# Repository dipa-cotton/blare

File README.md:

# blare
my annoying alarm clock :)

## purpose
i wanted to make this alarm clock to familiarize myself with C++ and the arduino IDE. i really enjoyed playing around with the pcb as well, it was a fun mini project!

## goals
i want to submit this to blare to hopefully get the pillowcase :) I'll sleep better knowing orpheus is watching over me... or i guess under me

## components
the main files are my PCB and Schematic made in kicad, and I have directories of my arduino code and my case's stl file as well :)

no ai was used in this project :))))))

## pictures

## BOM
- 6 Cherry MX Switches
- 1 LCD Display
- 1 Lolin C3 Mini
- 1 Buzzer
- 6 Diodes
- 3 Capacitors (already owned)
a more detailed list can be found in BOM.csv :)

## Journal
### Day 1: PCB
#### Hours Spent: 3
##### What did you do?:
Today, I used KiCAD to build the schematic for my alarm as well as routed the PCB. This took quite a bit of effort, and took me a couple of hours due to fixing ERC and DRC issues.

##### Why did you do it?:
I did this to create the PCB for my project, so it can be easily manufactured and used to make an alarm clock that is compact for its size :)

##### What problems did you face?:
I faced issues with ERC (electric rules checker), mostly unused pins lol. In the end though, with google by my side, I was able to figure out that the unused pins must have an x symbol at the end of them to prevent KiCAD from getting angered. In the images above, you can see the specific wiring of the components, as well as the final PCB. The PCB was the easy part, as routing was quite simple.

### Day 2: Code
#### Hours Spent: 4
##### What did you do?:
Today, I used the Arduino IDE to fully code the alarm clock. In my code, there are if statements that correspond each switch to a certain command, which displays what it does on the LCD as well. There are multiple commands, such as one that displays an undertale doggo, one that shows the weather, one that allows you to set an alarm time, one that shows the current time, and others as well. This code, once uploaded should hopefully turn the alarm clock into a working device, not just an alarm clock :)

##### Why did you do it?:
I did this with the goal of making something more complex than a simple alarm clock, but a device within itself that can be used for multiple purposes, sort of like a nightstand hub that tells you everything you need to know!

##### What problems did you face?:
I faced syntax issues with C++ as always, and I also didn't know how to display an image of the undertale doggo on the screen, but with guidance from google and a website that turned the image into a format that the c3 can understand, I was able to successfully use it to display an image when a certain button is pressed. In the future, I may try to add motion, or a lil gif of the guy jumping!

### Day 3: CAD
#### Hours Spent: 1
##### What did you do?:
Today, I used Fusion 360 to create a case for my alarm clock. I exported a step file of the pcb from KiCAD, imported it into Fusion as a mesh file, and created a case around it. This process made sure that everything is correctly spaced, and looks nice.

##### Why did you do it?:
I did this so the alarm clock isn't just a PCB with no case. It has a heart too, yknow? In the future, I'll make it look nicer, but once my PCB arrives, I'll make sure everything fits and make it look nicer.

##### What problems did you face?:
I didn't really face any issues, cuz I know Fusion 360 pretty well, but text always acts funny on my Mac so I just had to struggle with that for a minute or 2.

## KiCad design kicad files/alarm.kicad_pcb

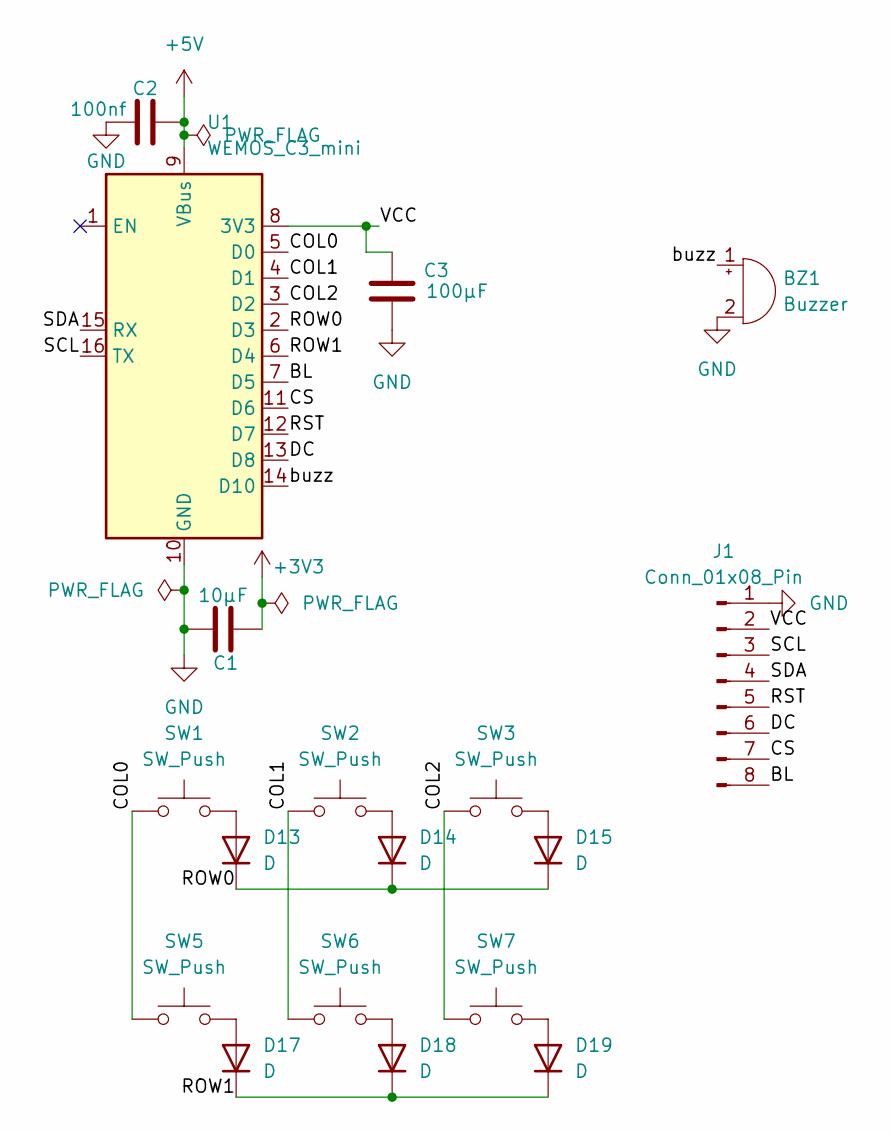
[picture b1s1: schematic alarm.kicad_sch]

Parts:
BZ1: Buzzer; Buzzer_12x9.5RM7.6
C1: 10µF; CP_Axial_L10.0mm_D4.5mm_P15.00mm_Horizontal
C2: 100nf; CP_Axial_L10.0mm_D4.5mm_P15.00mm_Horizontal
C3: 100µF; CP_Axial_L10.0mm_D4.5mm_P15.00mm_Horizontal
D13, D14, D15, D17, D18, D19: D; D_T-1_P10.16mm_Horizontal
J1: Conn_01x08_Pin; PinHeader_1x08_P2.54mm_Vertical
SW1, SW2, SW3, SW5, SW6, SW7: SW_Push; SW_Cherry_MX_1.00u_PCB
U1: WEMOS_C3_mini

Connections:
+3V3: C1.2
+5V: C2.2, U1.9 (VBus)
/BL: J1.8, U1.7 (D5)
/COL0: SW1.1, SW5.1, U1.5 (D0)
/COL1: SW2.1, SW6.1, U1.4 (D1)
/COL2: SW3.1, SW7.1, U1.3 (D2)
/CS: J1.7, U1.11 (D6)
/DC: J1.6, U1.13 (D8)
/ROW0: D13.1 (K), D14.1 (K), D15.1 (K), U1.2 (D3)
/ROW1: D17.1 (K), D18.1 (K), D19.1 (K), U1.6 (D4)
/RST: J1.5, U1.12 (D7)
/SCL: J1.3, U1.16 (TX)
/SDA: J1.4, U1.15 (RX)
/VCC: C3.1, J1.2, U1.8 (3V3)
/buzz: BZ1.1 (+), U1.14 (D10)
GND: BZ1.2 (-), C1.1, C2.1, C3.2, J1.1, U1.10 (GND)
unnamed: D13.2 (A), SW1.2
unnamed: D14.2 (A), SW2.2
unnamed: D15.2 (A), SW3.2
unnamed: D17.2 (A), SW5.2
unnamed: D18.2 (A), SW6.2
unnamed: D19.2 (A), SW7.2

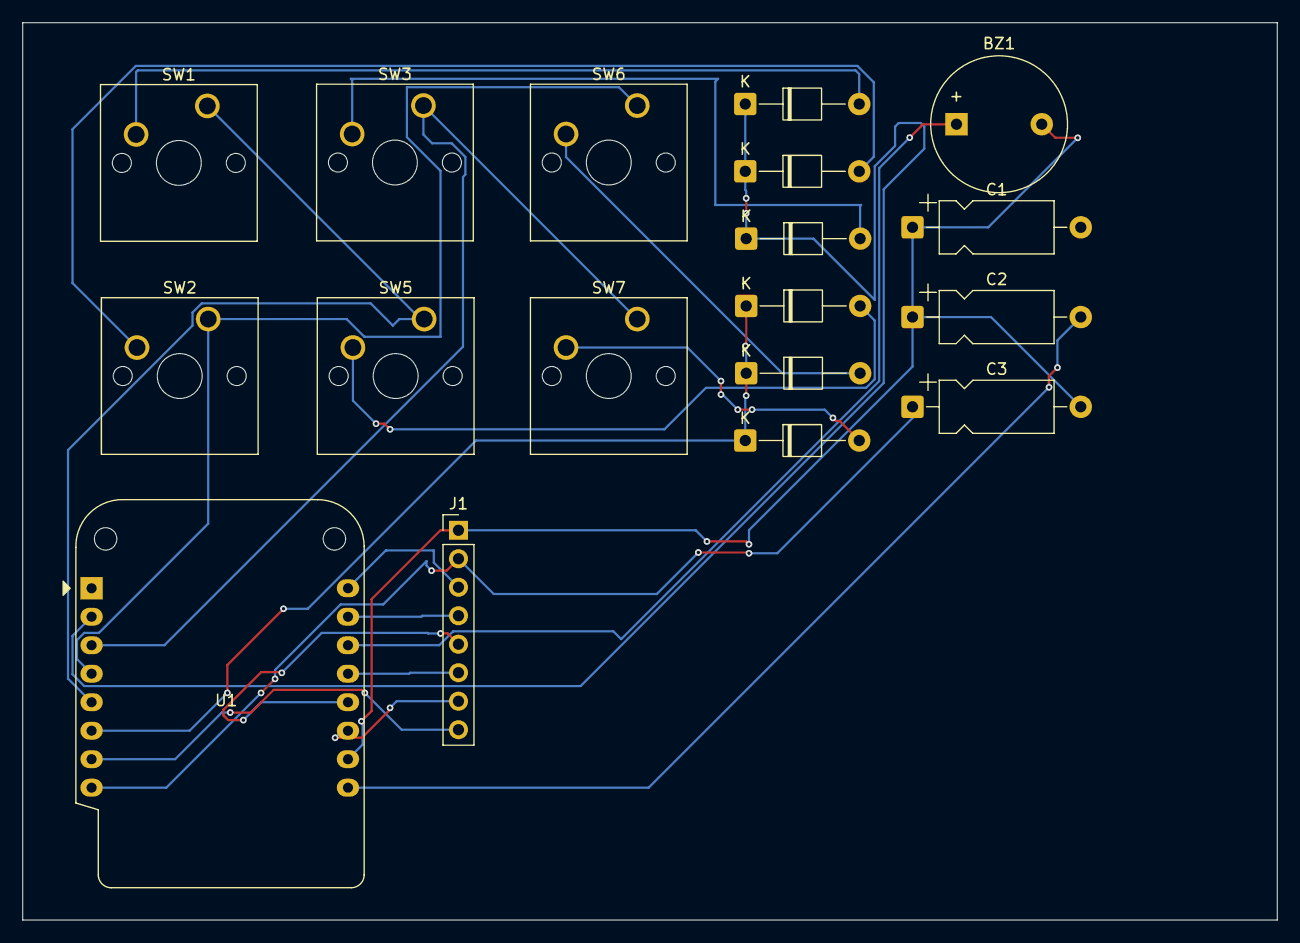
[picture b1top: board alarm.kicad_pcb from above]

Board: 2 copper layers, 111.8 x 80.0 mm, 18 parts (0 on the bottom side), 21 nets.
